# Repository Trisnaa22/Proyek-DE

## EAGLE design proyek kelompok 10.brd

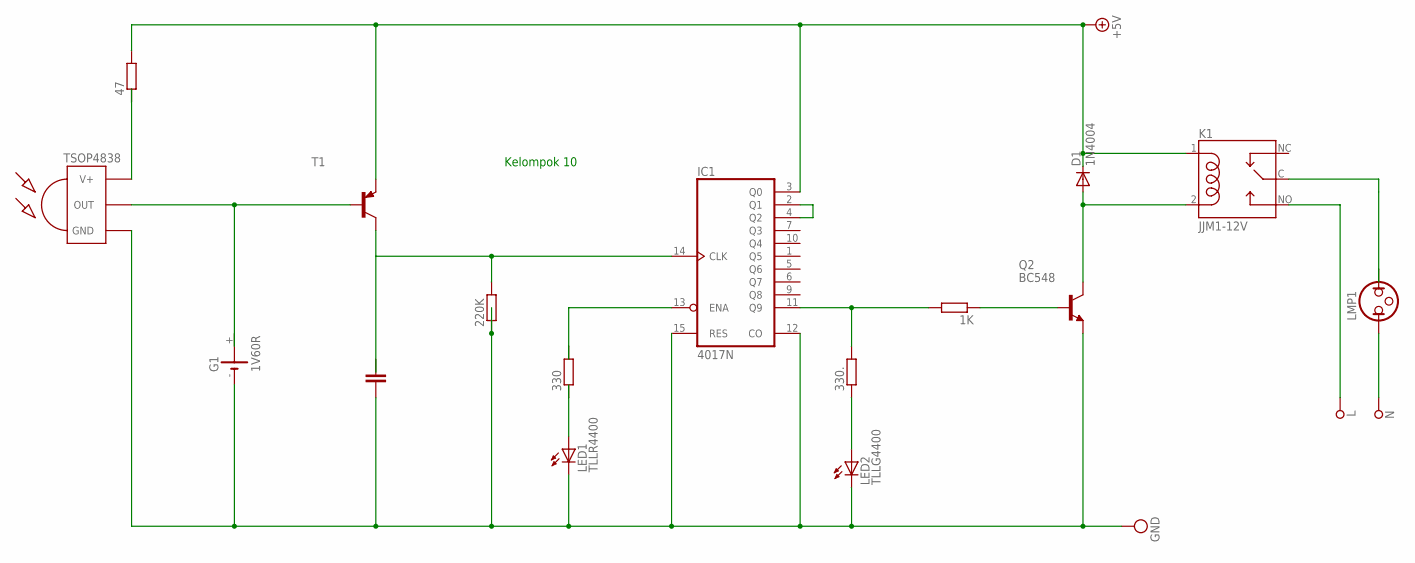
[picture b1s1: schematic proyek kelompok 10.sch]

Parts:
1K, 47, 220K, 330, 330.: R0207/10; 0207/10
D1: 1N4004; DO41-10
G1: 1V60R
IC1: 4017N; DIL16
K1: JJM1-12V; RELAY_JJM1-12V
L: SPECIAL_DRILL_0.1000; PAD_0.1000
LED1: TLLR4400; LED3MM
LED2: TLLG4400; LED3MM
LMP1: NEON; LDH-3R
N: SPECIAL_DRILL_0.1000; PAD_0.1000
Q2: BC548; TO92-EBC
T1: BC558A-PNP-TO92-EBC; TO92-EBC
U$1: TSOP4838; TSOP18XX

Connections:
47: 47.1, U$1.VCC (V+)
+5V: 47.2, D1.C, IC1.3 (Q0), K1.1 (C1), T1.E
unnamed: G1.+@1 (+), T1.B, U$1.OUT
unnamed: 220K.2, IC1.14 (CLK)
unnamed: K1.C (M), LMP1.2
unnamed: 330.1, LED1.A
unnamed: 1K.2, 330..2, IC1.11 (Q9)
unnamed: 330.2, IC1.13 (ENA)
unnamed: D1.A, K1.2 (C2), Q2.C
unnamed: LMP1.1, N.1
unnamed: K1.NO, L.1
unnamed: IC1.2 (Q1), IC1.4 (Q2)
unnamed: 1K.1, Q2.B
unnamed: 330..1, LED2.A
VDD: 220K.1, G1.-, IC1.12 (CO), IC1.15 (RES), IC1.16 (VDD), LED1.K (C), LED2.K (C), Q2.E, U$1.GND
VSS: IC1.8 (VSS)

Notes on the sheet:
Kelompok 10

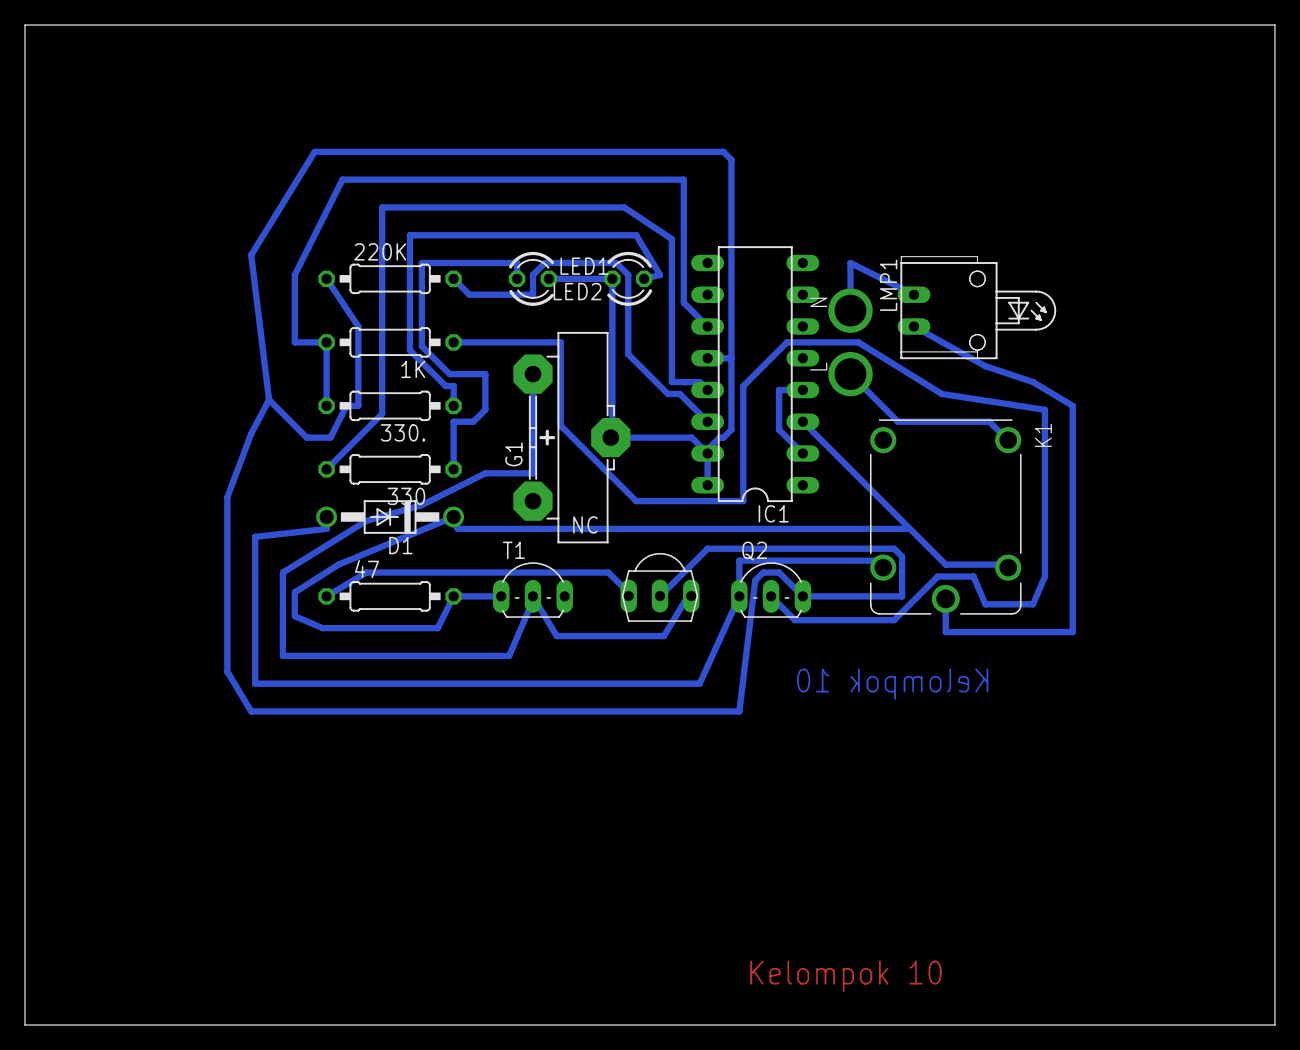
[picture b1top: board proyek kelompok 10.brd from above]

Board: 2 copper layers, 100.0 x 80.0 mm, 17 parts (0 on the bottom side), 15 nets.

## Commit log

2024-01-26 Proyek DE
